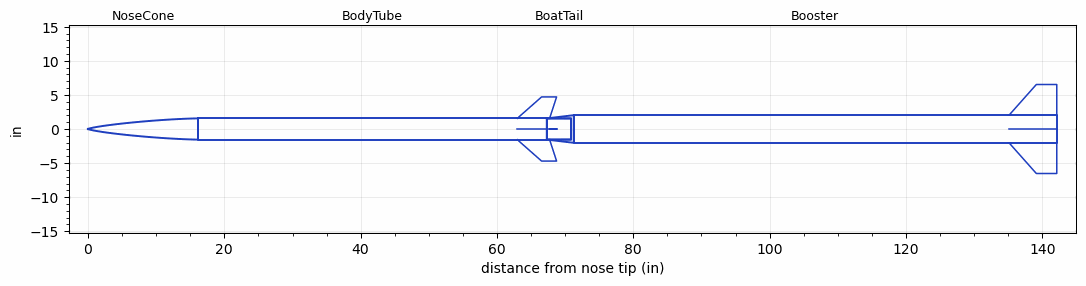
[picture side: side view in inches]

<RASAeroDocument>
 <FileVersion>2</FileVersion>
 <RocketDesign>
  <NoseCone>
   <Length>16.142</Length>
   <Diameter>3.11</Diameter>
   <Shape>Von Karman Ogive</Shape>
   <Location>0</Location>
  </NoseCone>
  <BodyTube>
   <Length>51.182</Length>
   <Diameter>3.11</Diameter>
   <Location>16.142</Location>
   <BoattailLength>3.543</BoattailLength>
   <BoattailRearDiameter>3.1</BoattailRearDiameter>
   <Overhang>0.3940001</Overhang>
   <Fin>
    <Count>4</Count>
    <Chord>4.75</Chord>
    <Span>3.15</Span>
    <SweepDistance>3.575</SweepDistance>
    <TipChord>2.2</TipChord>
    <Thickness>0.165</Thickness>
    <LERadius>0.01</LERadius>
    <Location>4.356</Location>
    <AirfoilSection>Hexagonal</AirfoilSection>
    <FX1>1</FX1>
    <FX3>1</FX3>
   </Fin>
   <Protuberance>
    <StreamlinedNoBaseDrag>0</StreamlinedNoBaseDrag>
    <StreamlinedWithBaseDrag>0</StreamlinedWithBaseDrag>
    <InclinedPlate1Angle>12.42</InclinedPlate1Angle>
    <InclinedPlate1FrontalArea>0.232</InclinedPlate1FrontalArea>
    <InclinedPlate2Angle>0</InclinedPlate2Angle>
    <InclinedPlate2FrontalArea>0</InclinedPlate2FrontalArea>
   </Protuberance>
  </BodyTube>
  <BoatTail>
   <Length>3.543</Length>
   <Diameter>3.11</Diameter>
   <RearDiameter>3.1</RearDiameter>
   <Location>67.324</Location>
  </BoatTail>
  <Booster>
   <Length>70.866</Length>
   <Diameter>4.055</Diameter>
   <InsideDiameter>3.11</InsideDiameter>
   <Location>67.324</Location>
   <ShoulderLength>3.937</ShoulderLength>
   <Fin>
    <Count>4</Count>
    <Chord>7</Chord>
    <Span>4.5</Span>
    <SweepDistance>4</SweepDistance>
    <TipChord>3</TipChord>
    <Thickness>0.165</Thickness>
    <LERadius>0.01</LERadius>
    <Location>7</Location>
    <AirfoilSection>Hexagonal</AirfoilSection>
    <FX1>1</FX1>
    <FX3>1</FX3>
   </Fin>
   <Protuberance>
    <StreamlinedNoBaseDrag>0</StreamlinedNoBaseDrag>
    <StreamlinedWithBaseDrag>0</StreamlinedWithBaseDrag>
    <InclinedPlate1Angle>12.42</InclinedPlate1Angle>
    <InclinedPlate1FrontalArea>0.232</InclinedPlate1FrontalArea>
    <InclinedPlate2Angle>0</InclinedPlate2Angle>
    <InclinedPlate2FrontalArea>0</InclinedPlate2FrontalArea>
   </Protuberance>
  </Booster>
  <Surface>Smooth Paint</Surface>
  <ModifiedBarrowman>False</ModifiedBarrowman>
  <Turbulence>True</Turbulence>
  <UseBooster1>False</UseBooster1>
  <UseBooster2>False</UseBooster2>
 </RocketDesign>
 <LaunchSite>
  <Altitude>2067</Altitude>
  <Pressure>0</Pressure>
  <RodAngle>0</RodAngle>
  <RodLength>20</RodLength>
  <Temperature>74</Temperature>
  <WindSpeed>0</WindSpeed>
 </LaunchSite>
 <Recovery>
  <Altitude1>1000</Altitude1>
  <Altitude2>1700</Altitude2>
  <DeviceType1>Parachute</DeviceType1>
  <DeviceType2>Parachute</DeviceType2>
  <Event1>True</Event1>
  <Event2>True</Event2>
  <Size1>9</Size1>
  <Size2>36</Size2>
  <EventType1>Apogee</EventType1>
  <EventType2>Altitude</EventType2>
  <CD1>1.75</CD1>
  <CD2>2.2</CD2>
 </Recovery>
 <SimulationList>
  <Simulation>
   <SustainerEngine>M2045-BS  (CTI)</SustainerEngine>
   <SustainerLaunchWt>20.6</SustainerLaunchWt>
   <SustainerNozzleDiameter>1.875</SustainerNozzleDiameter>
   <SustainerCG>44.19</SustainerCG>
   <SustainerIgnitionDelay>15</SustainerIgnitionDelay>
   <Booster1Engine>N1560-WH-MB-P  (CTI)</Booster1Engine>
   <Booster1LaunchWt>66</Booster1LaunchWt>
   <Booster1SeparationDelay>0</Booster1SeparationDelay>
   <Booster1IgnitionDelay>0</Booster1IgnitionDelay>
   <Booster1CG>90.74</Booster1CG>
   <Booster1NozzleDiameter>2.7</Booster1NozzleDiameter>
   <IncludeBooster1>True</IncludeBooster1>
   <Booster2Delay>0</Booster2Delay>
   <IncludeBooster2>False</IncludeBooster2>
   <TimetoApogee>114.7039</TimetoApogee>
   <MaxAltitude>157758.4</MaxAltitude>
   <MaxVelocity>3707.682</MaxVelocity>
  </Simulation>
 </SimulationList>
</RASAeroDocument>
